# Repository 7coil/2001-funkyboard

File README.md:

# 2001 Funkyboard

A British ISO Keyboard.

## How to do this yourself.

1. Use http://www.keyboard-layout-editor.com/ to look at `keyboard.json`
2. Shove the `keyboard.json` into https://kb.xyz.is/ to generate a KiCad PCB

## Using

KiCad.

## Licencing

WTFPL

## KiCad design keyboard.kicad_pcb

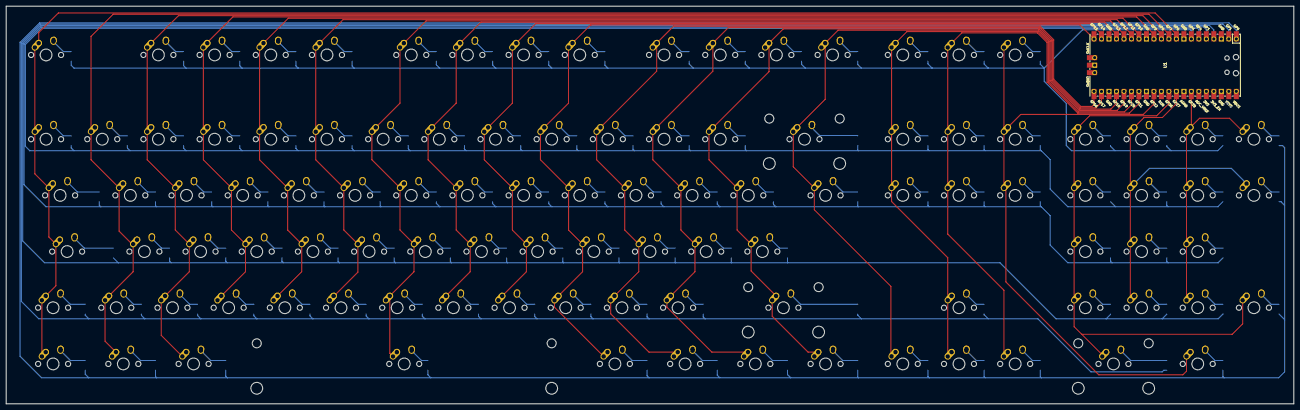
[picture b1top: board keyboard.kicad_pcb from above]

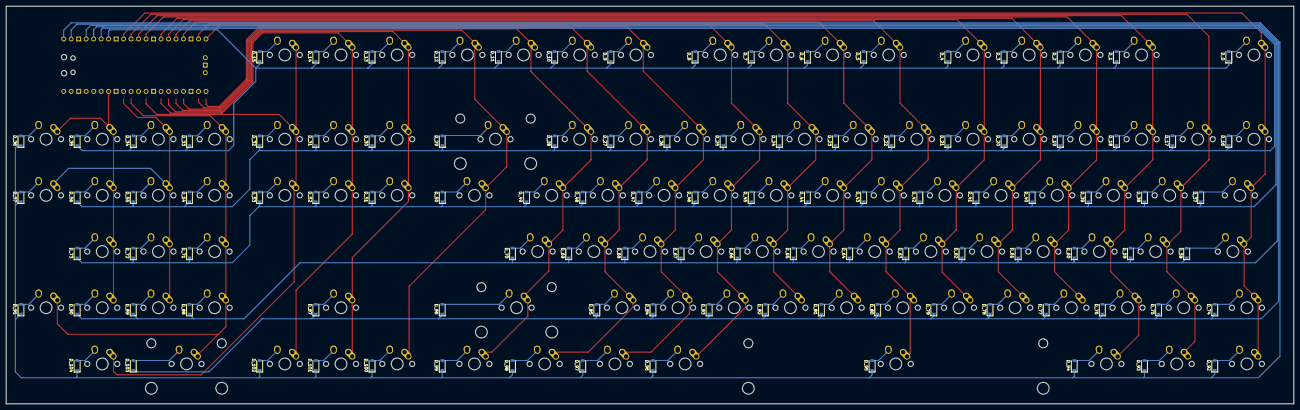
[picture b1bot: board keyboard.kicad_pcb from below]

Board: 2 copper layers, 436.6 x 134.8 mm, 211 parts (105 on the bottom side), 131 nets.

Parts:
D_0, D_1, D_2, D_3, D_4, D_5, D_6, D_7, D_8, D_9, D_10, D_11, D_12, D_13, D_14, D_15, D_16, D_17, D_18, D_19, D_20, D_21, D_22, D_23, D_24, D_25, D_26, D_27, D_28, D_29, D_30, D_31, D_32, D_33, D_34, D_35, D_36, D_37, D_38, D_39, D_40, D_41, D_42, D_43, D_44, D_45, D_46, D_47, D_48, D_49, D_50, D_51, D_52, D_53, D_54, D_55, D_56, D_57, D_58, D_59, D_60, D_61, D_62, D_63, D_64, D_65, D_66, D_67, D_68, D_69, D_70, D_71, D_72, D_73, D_74, D_75, D_76, D_77, D_78, D_79, D_80, D_81, D_82, D_83, D_84, D_85, D_86, D_87, D_88, D_89, D_90, D_91, D_92, D_93, D_94, D_95, D_96, D_97, D_98, D_99, D_100, D_101, D_102, D_103, D_104: D; D_SOD-123
K_0, K_1, K_2, K_3, K_4, K_5, K_6, K_7, K_8, K_9, K_10, K_11, K_12, K_13, K_14, K_15, K_16, K_17, K_18, K_19, K_20, K_21, K_22, K_23, K_24, K_25, K_26, K_27, K_28, K_30, K_31, K_32, K_33, K_34, K_35, K_36, K_38, K_39, K_40, K_41, K_42, K_43, K_44, K_45, K_46, K_47, K_48, K_49, K_51, K_52, K_53, K_54, K_55, K_56, K_57, K_59, K_60, K_61, K_62, K_63, K_64, K_65, K_66, K_67, K_68, K_69, K_70, K_71, K_72, K_73, K_75, K_76, K_77, K_78, K_79, K_80, K_81, K_82, K_83, K_84, K_85, K_87, K_88, K_89, K_90, K_91, K_100, K_101, K_102, K_104: KEYSW; MX-1U-NoLED
K_29, K_103: KEYSW; MX-2U-NoLED
K_37: KEYSW; MX-1.5U-NoLED
K_50, K_74, K_92, K_93, K_94, K_96, K_97, K_98, K_99: KEYSW; MX-1.25U-NoLED
K_58: KEYSW; MX-1.75U-NoLED
K_86: KEYSW; MX-2.75U-NoLED
K_95: KEYSW; MX-6.25U-NoLED
U1: Pico; RPi_Pico_SMD_TH

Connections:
unnamed: D_0.2 (A), K_0.2 (ROW)
unnamed: D_1.2 (A), K_1.2 (ROW)
unnamed: D_2.2 (A), K_2.2 (ROW)
unnamed: D_3.2 (A), K_3.2 (ROW)
unnamed: D_4.2 (A), K_4.2 (ROW)
unnamed: D_5.2 (A), K_5.2 (ROW)
unnamed: D_6.2 (A), K_6.2 (ROW)
unnamed: D_7.2 (A), K_7.2 (ROW)
unnamed: D_8.2 (A), K_8.2 (ROW)
unnamed: D_9.2 (A), K_9.2 (ROW)
unnamed: D_10.2 (A), K_10.2 (ROW)
unnamed: D_11.2 (A), K_11.2 (ROW)
unnamed: D_12.2 (A), K_12.2 (ROW)
unnamed: D_13.2 (A), K_13.2 (ROW)
unnamed: D_14.2 (A), K_14.2 (ROW)
unnamed: D_15.2 (A), K_15.2 (ROW)
unnamed: D_16.2 (A), K_16.2 (ROW)
unnamed: D_17.2 (A), K_17.2 (ROW)
unnamed: D_18.2 (A), K_18.2 (ROW)
unnamed: D_19.2 (A), K_19.2 (ROW)
unnamed: D_20.2 (A), K_20.2 (ROW)
unnamed: D_21.2 (A), K_21.2 (ROW)
unnamed: D_22.2 (A), K_22.2 (ROW)
unnamed: D_23.2 (A), K_23.2 (ROW)
unnamed: D_24.2 (A), K_24.2 (ROW)
unnamed: D_25.2 (A), K_25.2 (ROW)
unnamed: D_26.2 (A), K_26.2 (ROW)
unnamed: D_27.2 (A), K_27.2 (ROW)
unnamed: D_28.2 (A), K_28.2 (ROW)
unnamed: D_29.2 (A), K_29.2 (ROW)
unnamed: D_30.2 (A), K_30.2 (ROW)
unnamed: D_31.2 (A), K_31.2 (ROW)
unnamed: D_32.2 (A), K_32.2 (ROW)
unnamed: D_33.2 (A), K_33.2 (ROW)
unnamed: D_34.2 (A), K_34.2 (ROW)
unnamed: D_35.2 (A), K_35.2 (ROW)
unnamed: D_36.2 (A), K_36.2 (ROW)
unnamed: D_37.2 (A), K_37.2 (ROW)
unnamed: D_38.2 (A), K_38.2 (ROW)
unnamed: D_39.2 (A), K_39.2 (ROW)
unnamed: D_40.2 (A), K_40.2 (ROW)
unnamed: D_41.2 (A), K_41.2 (ROW)
unnamed: D_42.2 (A), K_42.2 (ROW)
unnamed: D_43.2 (A), K_43.2 (ROW)
unnamed: D_44.2 (A), K_44.2 (ROW)
unnamed: D_45.2 (A), K_45.2 (ROW)
unnamed: D_46.2 (A), K_46.2 (ROW)
unnamed: D_47.2 (A), K_47.2 (ROW)
unnamed: D_48.2 (A), K_48.2 (ROW)
unnamed: D_49.2 (A), K_49.2 (ROW)
unnamed: D_50.2 (A), K_50.2 (ROW)
unnamed: D_51.2 (A), K_51.2 (ROW)
unnamed: D_52.2 (A), K_52.2 (ROW)
unnamed: D_53.2 (A), K_53.2 (ROW)
unnamed: D_54.2 (A), K_54.2 (ROW)
unnamed: D_55.2 (A), K_55.2 (ROW)
unnamed: D_56.2 (A), K_56.2 (ROW)
unnamed: D_57.2 (A), K_57.2 (ROW)
unnamed: D_58.2 (A), K_58.2 (ROW)
unnamed: D_59.2 (A), K_59.2 (ROW)
unnamed: D_60.2 (A), K_60.2 (ROW)
unnamed: D_61.2 (A), K_61.2 (ROW)
unnamed: D_62.2 (A), K_62.2 (ROW)
unnamed: D_63.2 (A), K_63.2 (ROW)
unnamed: D_64.2 (A), K_64.2 (ROW)
unnamed: D_65.2 (A), K_65.2 (ROW)
unnamed: D_66.2 (A), K_66.2 (ROW)
unnamed: D_67.2 (A), K_67.2 (ROW)
unnamed: D_68.2 (A), K_68.2 (ROW)
unnamed: D_69.2 (A), K_69.2 (ROW)
unnamed: D_70.2 (A), K_70.2 (ROW)
unnamed: D_71.2 (A), K_71.2 (ROW)
unnamed: D_72.2 (A), K_72.2 (ROW)
unnamed: D_73.2 (A), K_73.2 (ROW)
unnamed: D_74.2 (A), K_74.2 (ROW)
unnamed: D_75.2 (A), K_75.2 (ROW)
unnamed: D_76.2 (A), K_76.2 (ROW)
unnamed: D_77.2 (A), K_77.2 (ROW)
unnamed: D_78.2 (A), K_78.2 (ROW)
unnamed: D_79.2 (A), K_79.2 (ROW)
unnamed: D_80.2 (A), K_80.2 (ROW)
unnamed: D_81.2 (A), K_81.2 (ROW)
unnamed: D_82.2 (A), K_82.2 (ROW)
unnamed: D_83.2 (A), K_83.2 (ROW)
unnamed: D_84.2 (A), K_84.2 (ROW)
unnamed: D_85.2 (A), K_85.2 (ROW)
unnamed: D_86.2 (A), K_86.2 (ROW)
unnamed: D_87.2 (A), K_87.2 (ROW)
unnamed: D_88.2 (A), K_88.2 (ROW)
unnamed: D_89.2 (A), K_89.2 (ROW)
unnamed: D_90.2 (A), K_90.2 (ROW)
unnamed: D_91.2 (A), K_91.2 (ROW)
unnamed: D_92.2 (A), K_92.2 (ROW)
unnamed: D_93.2 (A), K_93.2 (ROW)
unnamed: D_94.2 (A), K_94.2 (ROW)
unnamed: D_95.2 (A), K_95.2 (ROW)
unnamed: D_96.2 (A), K_96.2 (ROW)
unnamed: D_97.2 (A), K_97.2 (ROW)
unnamed: D_98.2 (A), K_98.2 (ROW)
unnamed: D_99.2 (A), K_99.2 (ROW)
unnamed: D_100.2 (A), K_100.2 (ROW)
unnamed: D_101.2 (A), K_101.2 (ROW)
unnamed: D_102.2 (A), K_102.2 (ROW)
unnamed: D_103.2 (A), K_103.2 (ROW)
unnamed: D_104.2 (A), K_104.2 (ROW)
col0: K_0.1 (COL), K_16.1 (COL), K_37.1 (COL), K_58.1 (COL), K_74.1 (COL), K_92.1 (COL), U1.9 (GPIO6)
col1: K_17.1 (COL), K_38.1 (COL), K_59.1 (COL), K_75.1 (COL), K_93.1 (COL), U1.10 (GPIO7)
col2: K_1.1 (COL), K_18.1 (COL), K_39.1 (COL), K_60.1 (COL), K_76.1 (COL), K_94.1 (COL), U1.11 (GPIO8)
col3: K_2.1 (COL), K_19.1 (COL), K_40.1 (COL), K_61.1 (COL), K_77.1 (COL), U1.12 (GPIO9)
col4: K_3.1 (COL), K_20.1 (COL), K_41.1 (COL), K_62.1 (COL), K_78.1 (COL), U1.14 (GPIO10)
col5: K_4.1 (COL), K_21.1 (COL), K_42.1 (COL), K_63.1 (COL), K_79.1 (COL), U1.15 (GPIO11)
col6: K_5.1 (COL), K_22.1 (COL), K_43.1 (COL), K_64.1 (COL), K_80.1 (COL), K_95.1 (COL), U1.16 (GPIO12)
col7: K_6.1 (COL), K_23.1 (COL), K_44.1 (COL), K_65.1 (COL), K_81.1 (COL), U1.17 (GPIO13)
col8: K_7.1 (COL), K_24.1 (COL), K_45.1 (COL), K_66.1 (COL), K_82.1 (COL), U1.19 (GPIO14)
col9: K_8.1 (COL), K_25.1 (COL), K_46.1 (COL), K_67.1 (COL), K_83.1 (COL), K_96.1 (COL), U1.20 (GPIO15)
col10: K_9.1 (COL), K_26.1 (COL), K_47.1 (COL), K_68.1 (COL), K_84.1 (COL), K_97.1 (COL), U1.21 (GPIO16)
col11: K_10.1 (COL), K_27.1 (COL), K_48.1 (COL), K_69.1 (COL), K_85.1 (COL), K_98.1 (COL), U1.22 (GPIO17)
col12: K_11.1 (COL), K_28.1 (COL), K_49.1 (COL), K_70.1 (COL), K_86.1 (COL), K_99.1 (COL), U1.24 (GPIO18)
col13: K_12.1 (COL), K_29.1 (COL), K_50.1 (COL), K_100.1 (COL), U1.25 (GPIO19)
col14: K_13.1 (COL), K_30.1 (COL), K_51.1 (COL), K_87.1 (COL), K_101.1 (COL), U1.26 (GPIO20)
col15: K_14.1 (COL), K_31.1 (COL), K_52.1 (COL), K_102.1 (COL), U1.27 (GPIO21)
col16: K_15.1 (COL), K_32.1 (COL), K_53.1 (COL), K_104.1 (COL), U1.29 (GPIO22)
col17: K_33.1 (COL), K_54.1 (COL), K_71.1 (COL), K_88.1 (COL), K_91.1 (COL), K_103.1 (COL), U1.31 (GPIO26_ADC0)
col18: K_34.1 (COL), K_55.1 (COL), K_57.1 (COL), K_72.1 (COL), K_89.1 (COL), U1.32 (GPIO27_ADC1)
col19: K_35.1 (COL), K_36.1 (COL), K_56.1 (COL), K_73.1 (COL), K_90.1 (COL), U1.34 (GPIO28_ADC2)
row0: D_0.1 (K), D_1.1 (K), D_2.1 (K), D_3.1 (K), D_4.1 (K), D_5.1 (K), D_6.1 (K), D_7.1 (K), D_8.1 (K), D_9.1 (K), D_10.1 (K), D_11.1 (K), D_12.1 (K), D_13.1 (K), D_14.1 (K), D_15.1 (K), D_33.1 (K), D_34.1 (K), D_35.1 (K), U1.7 (GPIO5)
row1: D_16.1 (K), D_17.1 (K), D_18.1 (K), D_19.1 (K), D_20.1 (K), D_21.1 (K), D_22.1 (K), D_23.1 (K), D_24.1 (K), D_25.1 (K), D_26.1 (K), D_27.1 (K), D_28.1 (K), D_29.1 (K), D_30.1 (K), D_31.1 (K), D_32.1 (K), D_54.1 (K), D_55.1 (K), D_56.1 (K), U1.6 (GPIO4)
row2: D_37.1 (K), D_38.1 (K), D_39.1 (K), D_40.1 (K), D_41.1 (K), D_42.1 (K), D_43.1 (K), D_44.1 (K), D_45.1 (K), D_46.1 (K), D_47.1 (K), D_48.1 (K), D_49.1 (K), D_50.1 (K), D_51.1 (K), D_52.1 (K), D_53.1 (K), D_71.1 (K), D_72.1 (K), D_73.1 (K), U1.5 (GPIO3)
row3: D_58.1 (K), D_59.1 (K), D_60.1 (K), D_61.1 (K), D_62.1 (K), D_63.1 (K), D_64.1 (K), D_65.1 (K), D_66.1 (K), D_67.1 (K), D_68.1 (K), D_69.1 (K), D_70.1 (K), D_88.1 (K), D_89.1 (K), D_90.1 (K), U1.4 (GPIO2)
row4: D_74.1 (K), D_75.1 (K), D_76.1 (K), D_77.1 (K), D_78.1 (K), D_79.1 (K), D_80.1 (K), D_81.1 (K), D_82.1 (K), D_83.1 (K), D_84.1 (K), D_85.1 (K), D_86.1 (K), D_87.1 (K), D_103.1 (K), U1.2 (GPIO1)
row5: D_36.1 (K), D_57.1 (K), D_91.1 (K), D_92.1 (K), D_93.1 (K), D_94.1 (K), D_95.1 (K), D_96.1 (K), D_97.1 (K), D_98.1 (K), D_99.1 (K), D_100.1 (K), D_101.1 (K), D_102.1 (K), D_104.1 (K), U1.1 (GPIO0)
